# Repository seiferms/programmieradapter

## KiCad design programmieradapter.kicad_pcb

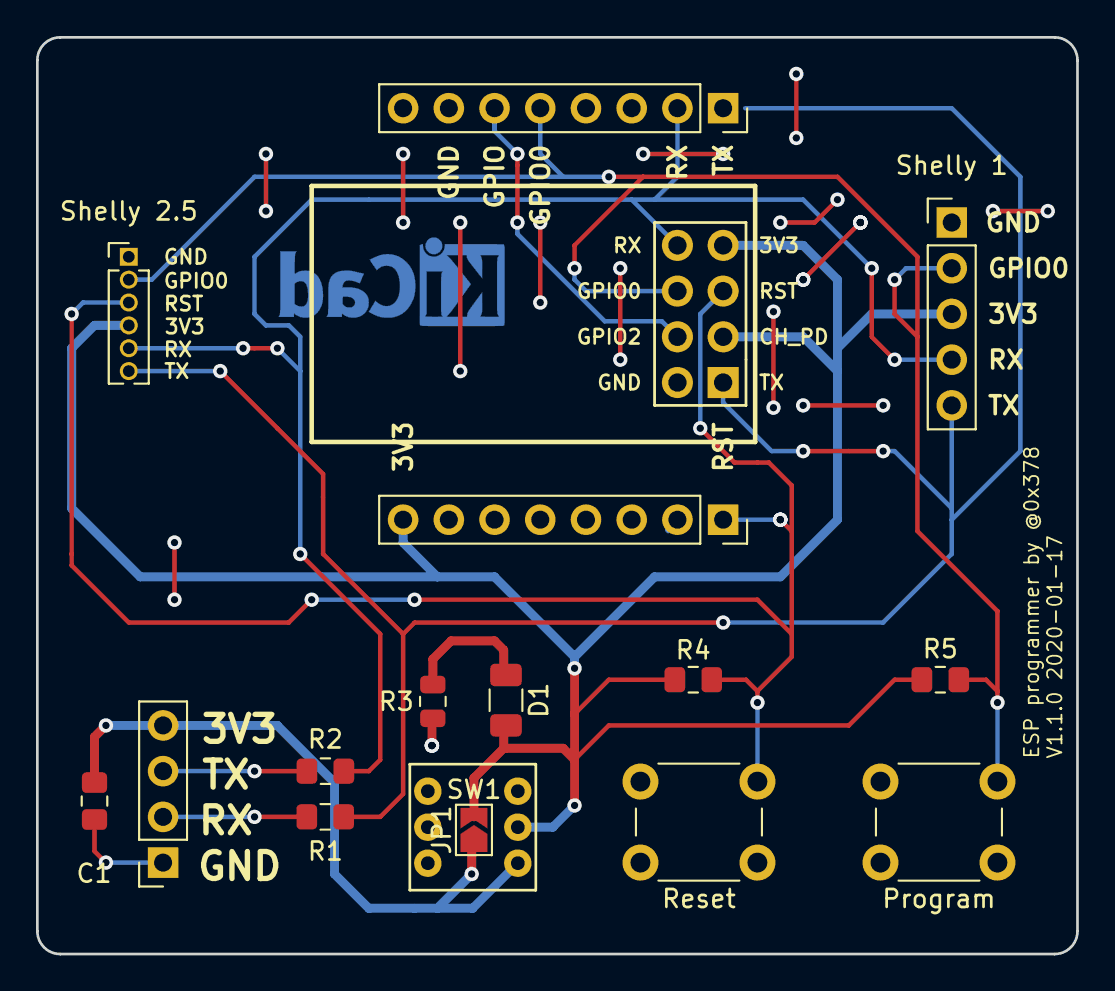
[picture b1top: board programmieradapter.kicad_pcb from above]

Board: 2 copper layers, 57.8 x 50.9 mm, 13 parts (0 on the bottom side), 8 nets.

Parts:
C1: 1uF; C_0805_2012Metric_Pad1.15x1.40mm_HandSolder
D1: LED; L_1206_3216Metric
JP1: SolderJumper_2_Open; SolderJumper-2_P1.3mm_Open_TrianglePad1.0x1.5mm
Program: SW_Push; SW_PUSH_6mm_H5mm
R1, R2: 1k; R_0805_2012Metric_Pad1.15x1.40mm_HandSolder
R3: 20; R_0805_2012Metric
R4, R5: 10k; R_0805_2012Metric_Pad1.15x1.40mm_HandSolder
Reset: SW_Push; SW_PUSH_6mm_H5mm
SW1: SW_Push; SW_7x7_6Pin
Shelly 1: Conn_01x05_Male; PinHeader_1x05_P2.54mm_Vertical
Shelly 2.5: Conn_01x06_Male; PinHeader_1x06_P1.27mm_Vertical

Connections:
3V3_CH430: C1.2, JP1.1, SW1.1
CH_PD: D1.2, JP1.2, R4.2, R5.2, SW1.2, Shelly 1.3, Shelly 2.5.4
GND: C1.1, Program.1, R3.2, Reset.1, Shelly 1.1, Shelly 2.5.1
GPIO0: Program.2, R5.1, Shelly 1.2, Shelly 2.5.2
unnamed: D1.1, R3.1
RST: R4.1, Reset.2, Shelly 2.5.3
RX_ESP: R2.1, Shelly 1.4, Shelly 2.5.5
TX_ESP: R1.1, Shelly 1.5, Shelly 2.5.6

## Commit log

2020-12-29 add version 1.1.0
2020-12-29 add missing connection to GND for shelly
2021-01-04 fix an error where the power indication LED did not have connection to GND
